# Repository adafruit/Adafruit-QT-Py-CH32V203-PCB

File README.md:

## Adafruit QT Py CH32V203 Dev Board with STEMMA QT PCB

<a href="http://www.adafruit.com/products/5996"><br/>
Click here to purchase one from the Adafruit shop</a>

PCB files for the Adafruit QT Py CH32V203 Dev Board with STEMMA QT. 

Format is EagleCAD schematic and board layout
* https://www.adafruit.com/product/5996

### Description

What a cutie pie! Or is it... a QT Py? This diminutive dev board features the powerful CH32V203 low-cost processor that's all the trend: based on RISC-V and cheaper than an 8-bit core! This little one is a great way to get started in the CH32x processor family, with everything you need to build many USB-based projects at an excellent price. 

The CH32V203G6 has a single 32-bit RISC-V core, running up to 144MHz, with 1-cycle multiply/divide. Inside is 10KB SRAM, 32KB single-cycle Flash as well as an additional 'external XIP' 224KB of Flash that can be used for program or data storage but  is not as fast as the 32KB. There's also extras you expect: ADC, timers, USB device, UART, I2C and SPI. 

However, please note that the CH32 series is not supported nearly-as-well as ATmega, ESP32, ATSAMD, STM32, or RP2040 chips that have a strong company-led development community. WCH is very "its a low cost chip, you figure it out" kind of company, and while there is some community-led development it is still best used by folks comfortable with having to use Makefiles, clone git repositories, edit configuration files, etc. It definitely does not run CircuitPython or Micropython, and Arduino support is very early. It's definitely not good for beginners! 

If you're interested in playing with the CH32V203, we've wrapped it up in a QT Py format. The pinout and shape is Seeed Xiao compatible, with castellated pads so you can solder it flat to a PCB. It comes with our favorite connector - the STEMMA QT, a chainable I2C port that can be used with any of our STEMMA QT sensors and accessories. We also added an RGB NeoPixel and both a reset button and 'bootloader enter' button that allows you to upload code over USB without a WCH LINKE or similar SWD programmer.

* Same size, form-factor, and pin-out as Seeed Xiao
* USB Type C connector - If you have only Micro B cables, this adapter will come in handy!
* CH32V203G8 RISC-V microcontroller core with 3.3V power/logic. Internal 144 MHz oscillator.
* Native USB Device - We do have USB CDC support via TinyUSB but its pretty chunky upload can also be done via USB
* Built in RGB NeoPixel LED
* 10 GPIO pins:
	* ADC input on all GPIOs
	* I2C port with STEMMA QT plug-n-play connector
	* Hardware UART
	* Hardware SPI
* 3.3V regulator with 600mA peak output
* Reset switch and bootloader switch for starting your project code over or entering USB ROM bootloader mode
* SWD data/clock pads on the bottom for advanced debugging usage
* Really really small

### License

Adafruit invests time and resources providing this open source design, please support Adafruit and open-source hardware by purchasing products from [Adafruit](https://www.adafruit.com)!

Designed by Limor Fried/Ladyada for Adafruit Industries.

Creative Commons Attribution/Share-Alike, all text above must be included in any redistribution. 
See license.txt for additional details.

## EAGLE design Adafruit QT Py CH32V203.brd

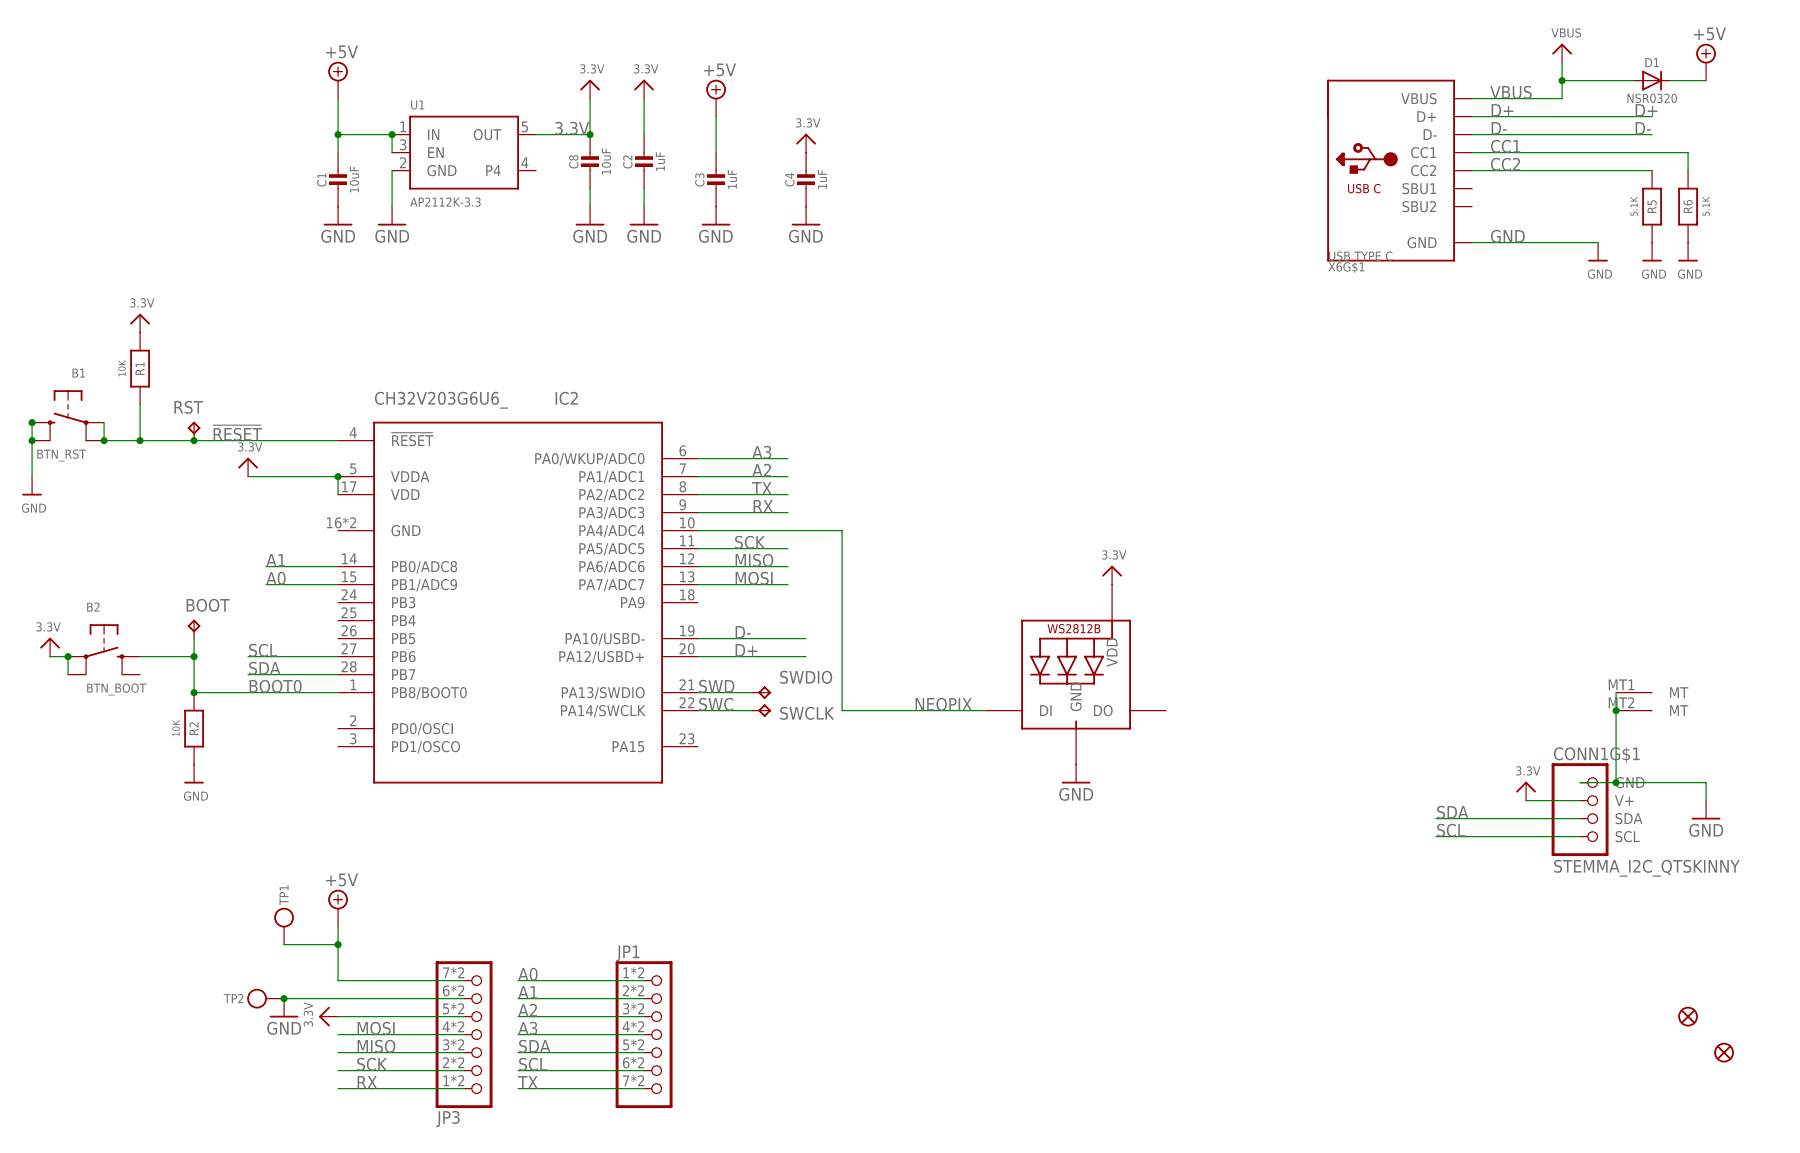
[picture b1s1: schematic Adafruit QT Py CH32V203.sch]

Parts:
B1: BTN_RST; BTN_RKB2_4.6X2.8
B2: BTN_BOOT; BTN_RKB2_4.6X2.8
BOOT: TPB1,27; B1,27
C1, C8: 10uF; _0805MP
C2, C3, C4: 1uF; _0402NO
CONN1: STEMMA_I2C_QTSKINNY; JST_SH4_SKINNY
D1: NSR0320; SOD-323_MINI
IC2: CH32V203G6U6_; QFN28_4MM_0.4MM
JP1, JP3: HEADER-1X7_CASTEL; 1X07_CASTEL
LED1: WS2812B_SK6805_1515; SK6805_1515
R1, R2: 10K; _0402NO
R5, R6: 5.1K; _0402NO
RST: TPB1,27; B1,27
SWCLK: SWCLK; B1,27
SWDIO: SWDIO; B1,27
TP1: TESTPOINT_PLUS13; TESTPOINT_PLUS_1X3MM
TP2: TESTPOINT_MINUS; TESTPOINT_MINUS_1X3MM
U1: AP2112K-3.3; SOT23-5; JLC_ROTATION 0
U$6, U$8: FIDUCIAL_1MM
X6: USB TYPE C; USB_C_CUSB31-CFM2AX-01-X

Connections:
3.3V: B2.A, B2.A' (P1), C2.1, C4.1, C8.1, CONN1.2 (V+), IC2.5 (VDDA), IC2.17 (VDD), JP3.5, JP3.5C (5), LED1.2 (VDD), R1.1, U1.5 (OUT)
!RESET: B1.A, B1.A' (P1), IC2.4 (!RESET), R1.2, RST.TP
+5V: C1.1, C3.1, D1.C, JP3.7, JP3.7C (7), TP1.P$1, U1.1 (IN), U1.3 (EN)
A0: IC2.15 (PB1/ADC9), JP1.1, JP1.1C (1)
A1: IC2.14 (PB0/ADC8), JP1.2, JP1.2C (2)
A2: IC2.7 (PA1/ADC1), JP1.3, JP1.3C (3)
A3: IC2.6 (PA0/WKUP/ADC0), JP1.4, JP1.4C (4)
BOOT0: B2.B (S), BOOT.TP, IC2.1 (PB8/BOOT0), R2.1
CC1: R6.2, X6.A5 (CC1)
CC2: R5.2, X6.B5 (CC2)
D+: IC2.20 (PA12/USBD+), X6.A6 (D+), X6.B6 (D+)
D-: IC2.19 (PA10/USBD-), X6.A7 (D-), X6.B7 (D-)
GND: B1.B (S), B1.B' (S1), C1.2, C2.2, C3.2, C4.2, C8.2, CONN1.1 (GND), CONN1.MT1 (MT), CONN1.MT2 (MT), IC2.16 (GND), IC2.THERMAL (GND), JP3.6, JP3.6C (6), LED1.4 (GND), R2.2, R5.1, R6.1, TP2.P$1, U1.2 (GND), X6.A1B12 (GND), X6.B1A12 (GND)
MISO: IC2.12 (PA6/ADC6), JP3.3, JP3.3C (3)
MOSI: IC2.13 (PA7/ADC7), JP3.4, JP3.4C (4)
NEOPIX: IC2.10 (PA4/ADC4), LED1.1 (DI)
RX: IC2.9 (PA3/ADC3), JP3.1, JP3.1C (1)
SCK: IC2.11 (PA5/ADC5), JP3.2, JP3.2C (2)
SCL: CONN1.4 (SCL), IC2.27 (PB6), JP1.6, JP1.6C (6)
SDA: CONN1.3 (SDA), IC2.28 (PB7), JP1.5, JP1.5C (5)
SWC: IC2.22 (PA14/SWCLK), SWCLK.TP
SWD: IC2.21 (PA13/SWDIO), SWDIO.TP
TX: IC2.8 (PA2/ADC2), JP1.7, JP1.7C (7)
VBUS: D1.A, X6.A4B9 (VBUS), X6.B4A9 (VBUS)

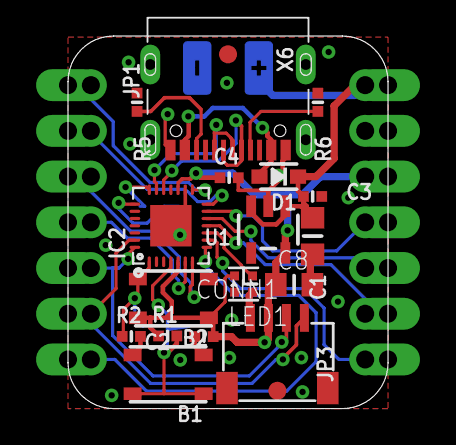
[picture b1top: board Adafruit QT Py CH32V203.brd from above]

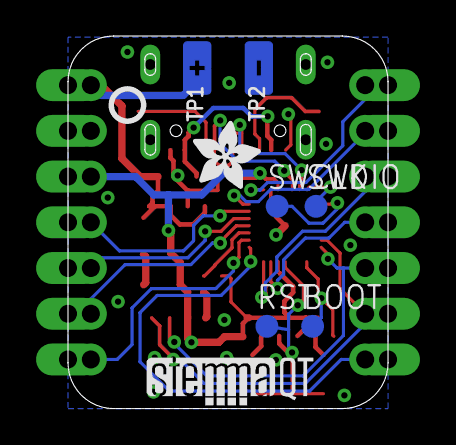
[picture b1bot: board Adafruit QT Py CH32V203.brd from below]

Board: 2 copper layers, 17.8 x 20.7 mm, 48 parts (26 on the bottom side), 24 nets.

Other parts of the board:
PLABEL0: PLABEL0
PLABEL1: PLABEL1
PLABEL2: PLABEL2
PLABEL3: PLABEL3
PLABEL4: PLABEL4
PLABEL5: PLABEL5
PLABEL6: PLABEL6
PLABEL7: PLABEL7
PLABEL8: PLABEL8
PLABEL9: PLABEL9
PLABEL10: PLABEL10
PLABEL11: PLABEL11
PLABEL12: PLABEL12
PLABEL13: PLABEL13
PLABEL14: PLABEL14
PLABEL15: PLABEL15
U$11: ADAFRUIT_3.5MM
U$12: PCBFEAT-REV-040
U$13: QTPY_CH32V203_BOT
U$21: STEMMAQT
U$23: QTPY_CH32V203_TOP

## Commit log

2024-07-22 cookiecutter
2024-09-09 prettypins

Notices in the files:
parts and their libraries:
microbuilder: This work is placed in the public domain, and may be freely used for commercial and non-commercial work with the following conditions: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
